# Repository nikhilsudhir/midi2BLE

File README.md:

<div align="center">

# midi2BLE

**Custom wireless MIDI adapter — ESP32-S3, LiPo powered, custom PCB**

A custom, battery-powered BLE MIDI adapter with a bespoke PCB and 3D-printed enclosure. Bridges a USB MIDI keyboard to a Mac over Bluetooth LE, eliminating the cable between instrument and computer.

[**View project page →**](https://nikhilsudhir.github.io/projects/midi2BT.html)

</div>

---

## Signal flow

<div align="center">

| **USB MIDI Keyboard** | | **ESP32-S3** | | **macOS** | | **DAW** |
|:---:|:---:|:---:|:---:|:---:|:---:|:---:|
| *(e.g. MPK Mini III)* | `── USB ──►` | *midi2BLE firmware* | `── BLE MIDI ──►` | *Audio MIDI Setup* | `──►` | *FL Studio* |

</div>

---

## Features

| | |
|---|---|
| **Wireless mode** | ESP32-S3 acts as USB host; MIDI data forwarded over BLE to macOS |
| **Passthrough mode** | Keyboard connected directly to upstream USB-C via hardware switch — ESP32 out of data path |
| **USB MIDI host** | Enumerates any class-compliant USB MIDI controller — no driver needed |
| **BLE MIDI peripheral** | Apple BLE MIDI spec, appears as a native MIDI port in Audio MIDI Setup |
| **MIDI panic** | On USB disconnect, sends Note Off + CC 123/120 for every active note on all 16 channels |
| **Auto-advertising** | Restarts BLE advertising automatically on every disconnect or reboot |
| **OLED display** | SPI-connected display shows mode, BLE status, battery %, and estimated runtime |
| **Battery management** | LiPo charge, power-path control, and ADC-based battery sense |

---

## Hardware

### Electronics

| Component | Part | Role |
|---|---|---|
| MCU / BLE | ESP32-S3-WROOM-1-N8 | Application processor, USB host, BLE MIDI |
| LiPo charger | BQ24079RGTT | 1-cell USB-C LiPo charging with power path |
| Buck regulator | TPS62162DSG | 3.3 V system rail |
| Boost converter | TLV61047DDC | 5 V VBUS supply for keyboard (wireless mode) |
| Power mux | TPS2116DRL | Battery / USB-C power-path switching |
| USB switch | TS3USB30EDGSR | Routes keyboard D+/D− to ESP32 or upstream port |
| USB ESD | PRTR5V0U2X | ESD protection on USB lines |
| Display | SPI OLED | Mode, connection status, battery info |

> Tested with an **Akai MPK Mini III**. Any USB class-compliant MIDI device should work.

### PCB

| | |
|---|---|
| Dimensions | 100 × 40 mm |
| Layers | 4 |
| Stackup | JLCPCB JLC04161H-7628 |
| Surface finish | HASL |
| Soldermask | Black |
| Mounting holes | M2.5 |

---

## Repository structure

- `main/` — Firmware (ESP-IDF / C) — see [main/README.md](main/README.md)
- `hardware/`
  - `ecad/` — KiCad schematic & PCB layout — see [hardware/ecad/README.md](hardware/ecad/README.md)
  - `mcad/` — Fusion 360 enclosure — see [hardware/mcad/README.md](hardware/mcad/README.md)
- `CMakeLists.txt`
- `sdkconfig.defaults`

---

## Build status

| Component | Status |
|---|---|
| Firmware | ✅ Complete |
| Schematic | ✅ Complete |
| PCB layout | ✅ Complete |
| Enclosure | ✅ Complete |

---

<div align="center">

[nikhilsudhir.github.io](https://nikhilsudhir.github.io/projects/midi2BLE.html)

</div>

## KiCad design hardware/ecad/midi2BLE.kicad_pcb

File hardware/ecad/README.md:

# midi2BLE

## Overview

This device is a portable USB-to-BLE MIDI bridge designed to interface with USB MIDI controllers such as the Akai MPK Mini III.

It supports two user-selectable modes:

* Wireless BLE MIDI operation
* Wired USB passthrough operation

The device is battery powered with USB-C charging and includes an onboard OLED display for status and battery information.

---

## Operating Modes

### 1. Wireless Mode

In this mode, the device acts as a BLE MIDI bridge.

#### Behavior

* ESP32-S3 operates as a USB host
* MIDI data is read from the keyboard and transmitted via BLE
* Device is powered from internal LiPo battery
* OLED displays:

  * battery percentage
  * estimated runtime
  * BLE connection status
  * keyboard connection status

#### Power

* Battery supplies system power
* Optional charging via USB-C

---

### 2. Passthrough Mode

In this mode, the device behaves as a direct USB cable between the keyboard and a computer.

#### Behavior

* Keyboard is directly connected to upstream USB-C port via hardware switching
* ESP32 is not part of the USB data path
* BLE functionality is disabled
* OLED remains active and displays:

  * "WIRED MODE"
  * charging status
  * battery percentage

#### Power

* System is powered from upstream USB-C
* Battery does NOT power the system
* Battery may still be charged

---

## Mode Selection

* A physical switch selects between:

  * WIRELESS
  * WIRED
* The switch is authoritative
* Mode switching is NOT live
* Device must be restarted after changing modes

---

## Ports

### Upstream USB-C Port

* Used for:

  * charging the device
  * connecting to a computer in passthrough mode
* Supplies system power when connected

### Keyboard USB-C Port

* Used to connect the MIDI controller
* Behavior depends on mode:

  * Wireless: connected to ESP32 USB host
  * Passthrough: connected directly to upstream USB-C

---

## Power Architecture

* 1-cell LiPo battery
* USB-C charging input
* Power-path design allows:

  * operation while charging
  * seamless transition between power sources

### Power Priorities

#### Wireless Mode

1. Battery powers system
2. USB-C supplements or charges battery

#### Passthrough Mode

1. Upstream USB-C powers system
2. Battery is isolated from load
3. Battery may still charge

---

## USB Routing

### Wireless Mode

* Keyboard D+/D- connected to ESP32 USB host

### Passthrough Mode

* Keyboard D+/D- connected directly to upstream USB-C port

This is implemented using a USB 2.0 switch/multiplexer.

---

## Keyboard Power (VBUS)

### Wireless Mode

* Supplied by internal 5V boost converter

### Passthrough Mode

* Supplied directly from upstream USB-C VBUS

---

## Display (OLED)

* SPI-connected monochrome OLED display
* Displays:

  * battery percentage
  * estimated runtime
  * current mode
  * connection status

---

## Firmware Behavior

### Wireless Mode

* USB host enabled
* BLE MIDI enabled
* MIDI data forwarded USB → BLE

### Passthrough Mode

* USB host disabled
* BLE disabled
* ESP32 used only for UI/status

---

## V1 Scope

### Included

* BLE MIDI output
* USB passthrough
* battery operation
* USB-C charging
* OLED display
* manual mode switch

### Excluded

* custom RF protocols
* MIDI remapping
* display UI complexity
* automatic mode switching
* USB hub functionality

---

## Hardware Design

The schematic and PCB layout are both complete. The design is implemented in **KiCad 10.0**.

| | |
|---|---|
| Revision | 1 |
| Schematic date | 2026-04-11 |
| PCB date | 2026-04-12 |

The schematic is split across seven sheets:

| Sheet | Description |
|---|---|
| Root | Top-level block diagram and inter-sheet connections |
| Power | LiPo charging, buck/boost regulation, and power-path control |
| ESP32_S3 | ESP32-S3-WROOM-1 module, decoupling, and GPIO assignments |
| USB Data | USB 2.0 data switching between keyboard and upstream port |
| VBUS Switching | 5V VBUS supply selection for the keyboard port |
| OLED UI | SPI OLED display and mode select switch |
| Battery Sense | Resistor divider and ADC input for battery voltage measurement |

### Key ICs

| IC | Part | Function |
|---|---|---|
| U1 | ESP32-S3-WROOM-1 | Main MCU + Wi-Fi/BLE module |
| U2 | BQ24074RGTT | 1-cell LiPo charger |
| U3 | TPS62162DSG | 3.3 V synchronous buck regulator |
| U4 | TLV61047DDC | 5 V boost converter (keyboard VBUS in wireless mode) |
| U5 | TPS2116DRL | Dual-input power mux (battery vs. USB-C power path) |
| U6 | TS3USB30EDGSR | USB 2.0 high-speed switch (keyboard data routing) |
| U7 | PRTR5V0U2X | USB ESD protection |

### PCB

The PCB is laid out in KiCad. All components are placed and fully routed.

**Board dimensions:** 75 × 40mm  
**Thickness:** 1.6mm  
**Layers:** 4  

#### Stackup

| Layer | Type | Thickness | Material |
|---|---|---|---|
| F.Cu | Signal | 35µm | Copper |
| Dielectric 1 | Prepreg | 0.1mm | FR4 |
| In1.Cu | GND plane | 35µm | Copper |
| Dielectric 2 | Core | 1.24mm | FR4 |
| In2.Cu | 3.3V power plane | 35µm | Copper |
| Dielectric 3 | Prepreg | 0.1mm | FR4 |
| B.Cu | Signal | 35µm | Copper |

Inner layers are solid copper fills: In1 = GND, In2 = SYS_3V3.

**Test points:** TP1–TP6  
**Via size:** 0.45mm diameter, 0.2mm drill

---

## Summary

This V1 design prioritizes:

* simplicity
* reliability
* clear user control

The system uses a manual mode switch and hardware-level USB routing to ensure predictable behavior and robust operation.

**Current status:** Schematic and PCB layout complete. Ready for fabrication review.

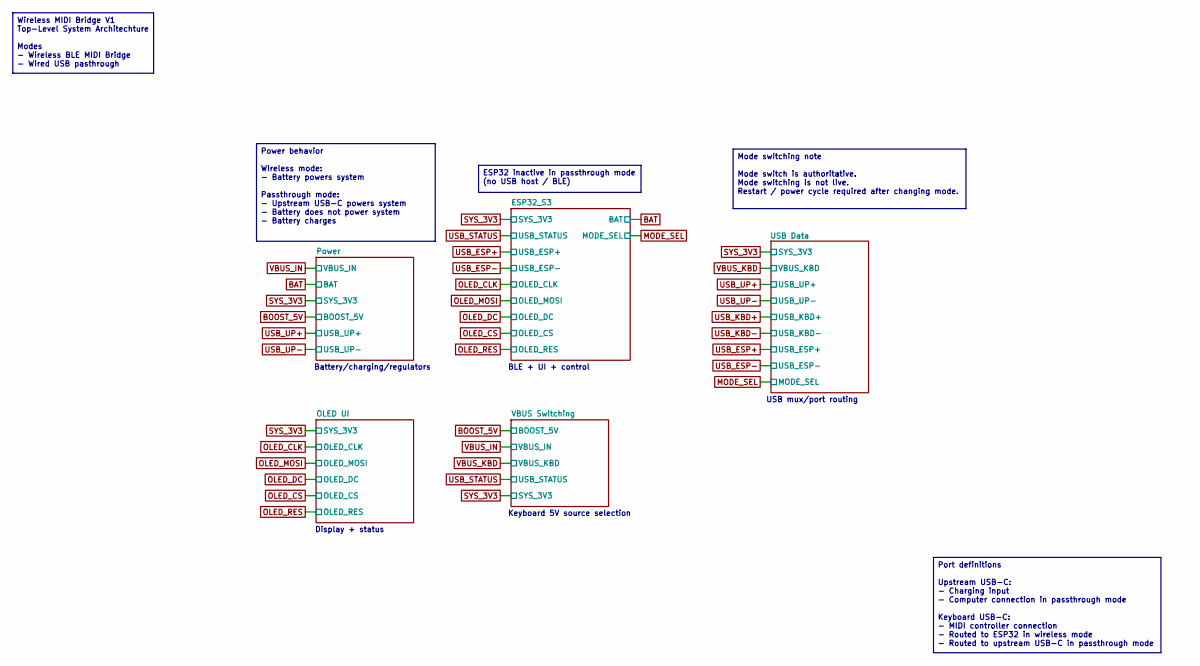
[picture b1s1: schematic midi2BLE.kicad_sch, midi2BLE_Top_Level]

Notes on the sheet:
Battery/charging/regulators
Keyboard 5V source selection
USB mux/port routing
Display + status
BLE + UI + control
Wireless MIDI Bridge V1 Top-Level System Architechture Modes - Wireless BLE MIDI Bridge - Wired USB pasthrough
Port definitions Upstream USB-C: - Charging input - Computer connection in passthrough mode Keyboard USB-C: - MIDI controller connection - Routed to ESP32 in wireless mode - Routed to upstream USB-C in passthrough mode
Mode switching note Mode switch is authoritative. Mode switching is not live. Restart / power cycle required after changing mode.
Power behavior Wireless mode: - Battery powers system Passthrough mode: - Upstream USB-C powers system - Battery does not power system - Battery charges
ESP32 inactive in passthrough mode (no USB host / BLE)

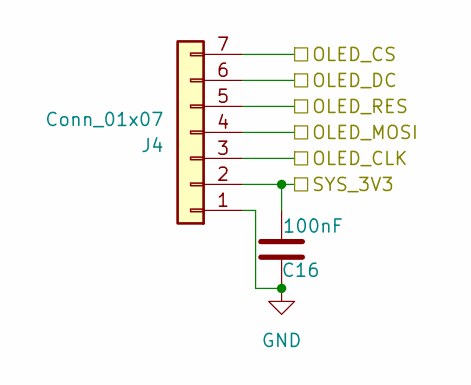
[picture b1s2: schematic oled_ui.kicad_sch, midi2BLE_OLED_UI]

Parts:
C16: 100nF; C_0603_1608Metric
J4: Conn_01x07; JST_EH_B7B-EH-A_1x07_P2.50mm_Vertical

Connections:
GND: C16.2, J4.1; also elsewhere on the board
OLED_CLK: J4.3; also elsewhere on the board
OLED_CS: J4.7; also elsewhere on the board
OLED_DC: J4.6; also elsewhere on the board
OLED_MOSI: J4.4; also elsewhere on the board
OLED_RES: J4.5; also elsewhere on the board
SYS_3V3: C16.1, J4.2; also elsewhere on the board

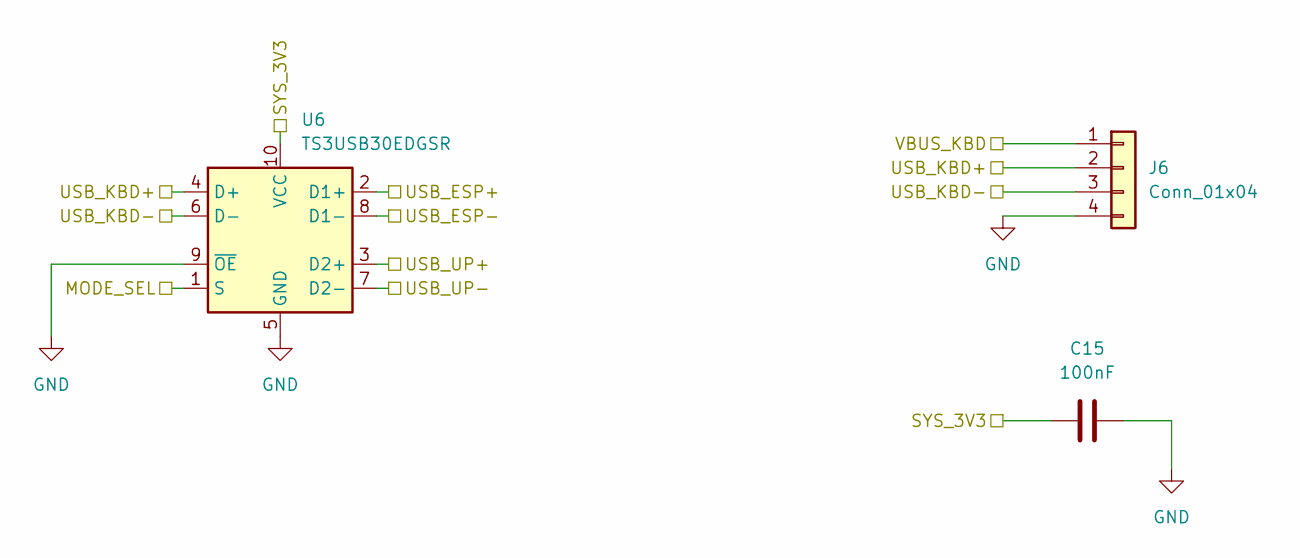
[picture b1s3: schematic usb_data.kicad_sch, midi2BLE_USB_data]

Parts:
C15: 100nF; C_0603_1608Metric
J6: Conn_01x04; JST_PH_B4B-PH-K_1x04_P2.00mm_Vertical
U6: TS3USB30EDGSR; TSSOP-10_3x3mm_P0.5mm

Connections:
GND: C15.1, J6.4, U6.5 (GND), U6.9 (~OE); also elsewhere on the board
MODE_SEL: U6.1 (S); also elsewhere on the board
SYS_3V3: C15.2, U6.10 (VCC); also elsewhere on the board
USB_ESP+: U6.2 (D1+); also elsewhere on the board
USB_ESP-: U6.8 (D1-); also elsewhere on the board
USB_KBD+: J6.2, U6.4 (D+)
USB_KBD-: J6.3, U6.6 (D-)
USB_UP+: U6.3 (D2+); also elsewhere on the board
USB_UP-: U6.7 (D2-); also elsewhere on the board
VBUS_KBD: J6.1; also elsewhere on the board

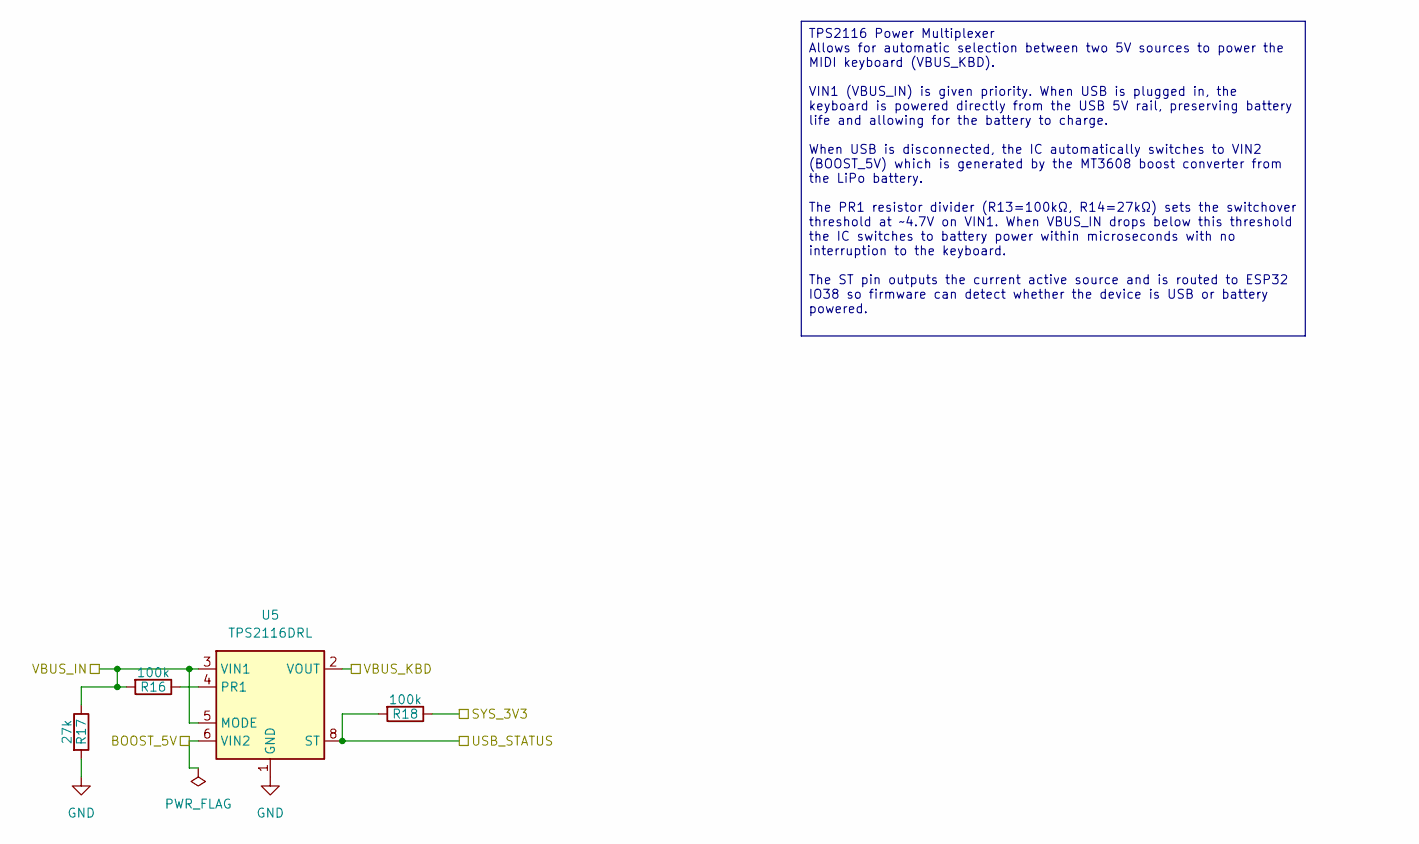
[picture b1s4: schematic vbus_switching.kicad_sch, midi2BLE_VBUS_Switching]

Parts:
R16, R18: 100k; R_0603_1608Metric
R17: 27k; R_0603_1608Metric
U5: TPS2116DRL; SOT-583-8

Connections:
BOOST_5V: U5.6 (VIN2); also elsewhere on the board
GND: R17.2, U5.1 (GND); also elsewhere on the board
unnamed: R16.1, U5.4 (PR1)
SYS_3V3: R18.1; also elsewhere on the board
USB_STATUS: R18.2, U5.8 (ST); also elsewhere on the board
VBUS_IN: R16.2, R17.1, U5.3 (VIN1), U5.5 (MODE); also elsewhere on the board
VBUS_KBD: U5.2 (VOUT), U5.7 (VOUT); also elsewhere on the board

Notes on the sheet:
TPS2116 Power Multiplexer Allows for automatic selection between two 5V sources to power the MIDI keyboard (VBUS_KBD). VIN1 (VBUS_IN) is given priority. When USB is plugged in, the keyboard is powered directly from the USB 5V rail, preserving battery life and allowing for the battery to charge. Whe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

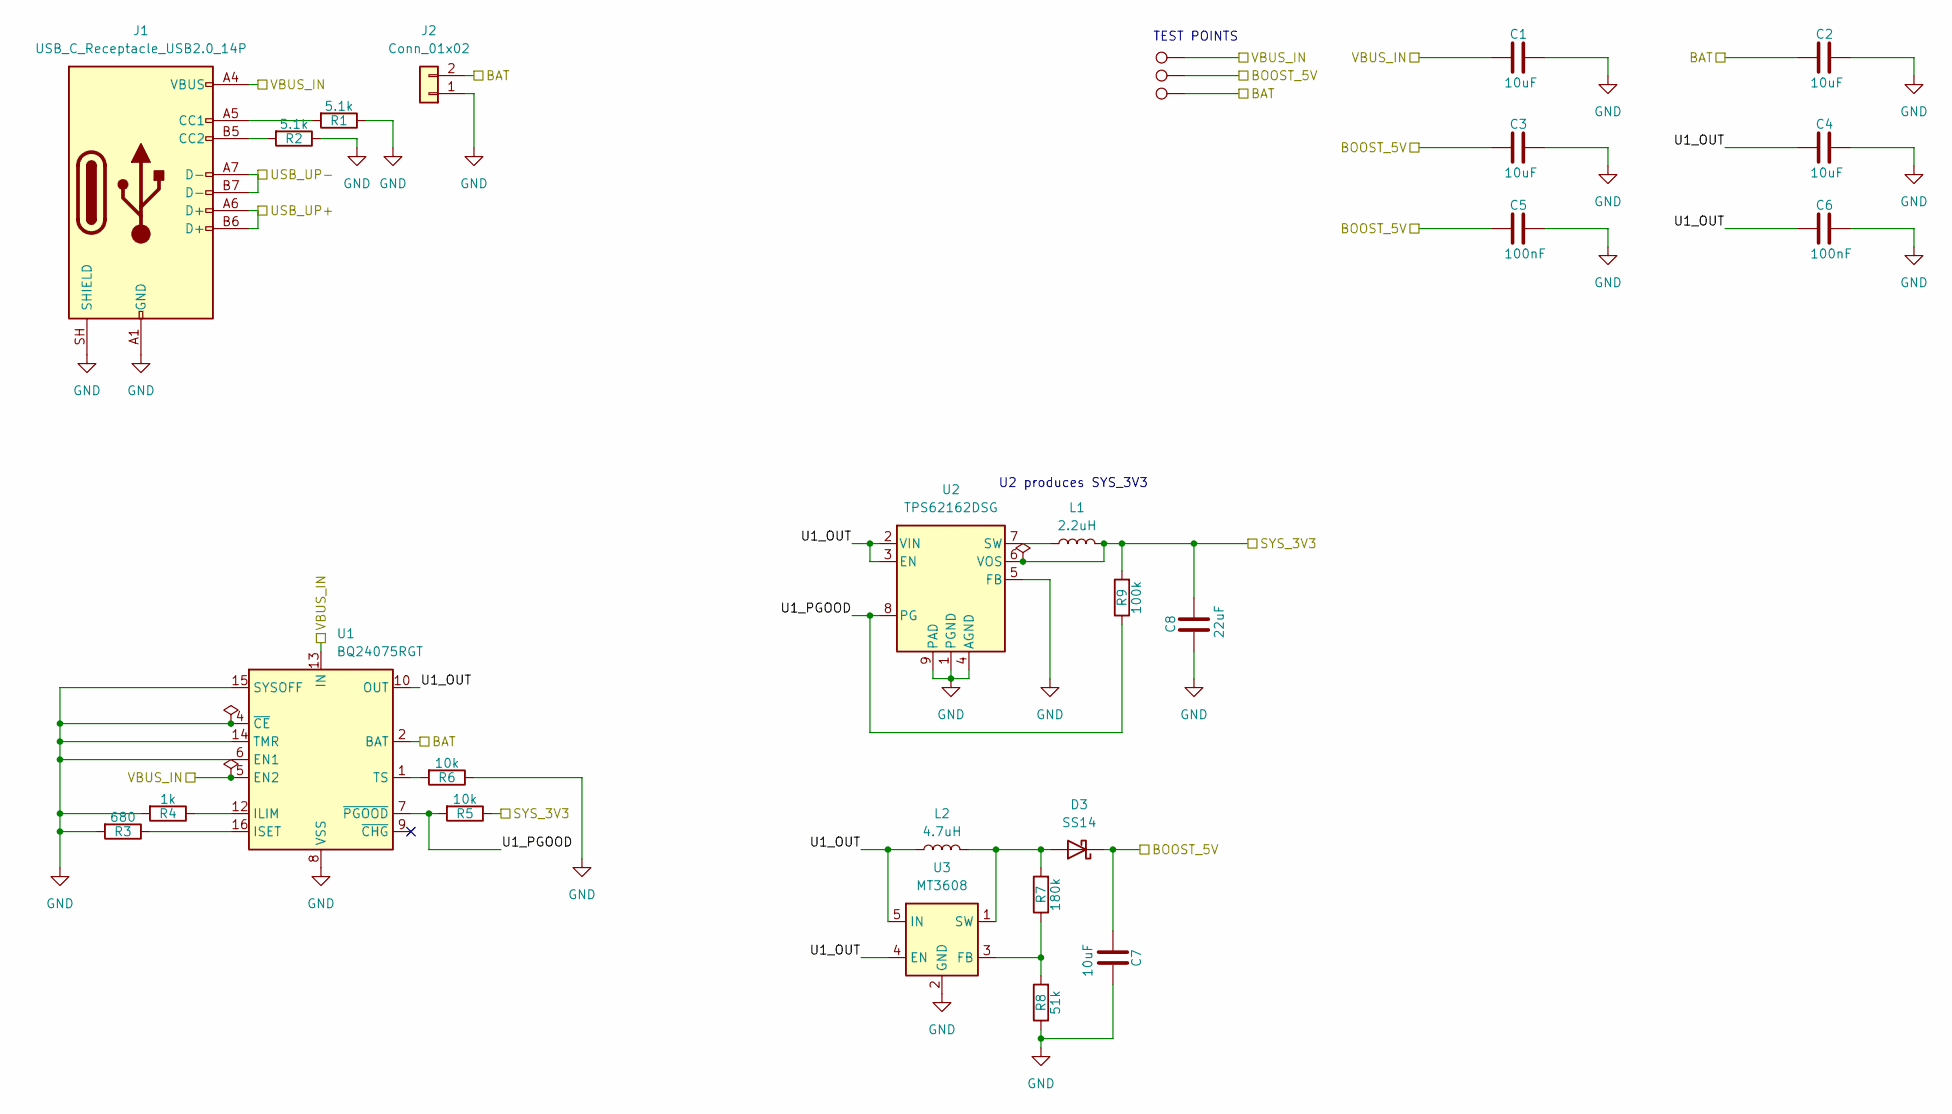
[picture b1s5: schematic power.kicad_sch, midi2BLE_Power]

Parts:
C1, C2, C3, C4, C7: 10uF; C_0603_1608Metric
C5, C6: 100nF; C_0603_1608Metric
C8: 22uF; C_0603_1608Metric
D3: SS14; D_SMA
J1: USB_C_Receptacle_USB2.0_14P; USB_C_Receptacle_G-Switch_GT-USB-7010ASV
J2: Conn_01x02; JST_PH_B2B-PH-K_1x02_P2.00mm_Vertical
L1: 2.2uH; L_1008_2520Metric
L2: 4.7uH; L_1008_2520Metric
R1, R2: 5.1k; R_0603_1608Metric
R3: 680; R_0603_1608Metric
R4: 1k; R_0603_1608Metric
R5, R6: 10k; R_0603_1608Metric
R7: 180k; R_0603_1608Metric
R8: 51k; R_0603_1608Metric
R9: 100k; R_0603_1608Metric
TP7, TP8, TP9: TestPoint; TestPoint_THTPad_D1.0mm_Drill0.5mm
U1: BQ24075RGT; VQFN-16-1EP_3x3mm_P0.5mm_EP1.6x1.6mm
U2: TPS62162DSG; WSON-8-1EP_2x2mm_P0.5mm_EP0.9x1.6mm_ThermalVias
U3: MT3608; SOT-23-6

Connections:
/Power/U1_OUT: C4.2, C6.2, L2.1, U1.10 (OUT), U1.11 (OUT), U2.2 (VIN), U2.3 (EN), U3.4 (EN), U3.5 (IN)
/Power/U1_PGOOD: R5.2, R9.1, U1.7 (~PGOOD), U2.8 (PG)
BAT: C2.2, J2.2, TP9.1 (1_1), U1.2 (BAT), U1.3 (BAT); also elsewhere on the board
BOOST_5V: C3.2, C5.2, C7.2, D3.1 (K), TP8.1 (1_1); also elsewhere on the board
GND: C1.1, C2.1, C3.1, C4.1, C5.1, C6.1, C7.1, C8.2, J1.A1 (GND), J1.A12 (GND), J1.B1 (GND), J1.B12 (GND), J1.SH (SHIELD), J2.1, R1.1, R2.1, R3.2, R4.2, R6.1, R8.1, U1.4 (~CE), U1.6 (EN1), U1.8 (VSS), U1.14 (TMR), U1.15 (SYSOFF), U1.17 (VSS), U2.1 (PGND), U2.4 (AGND), U2.5 (FB), U2.9 (PAD), U3.2 (GND); also elsewhere on the board
unnamed: D3.2 (A), L2.2, R7.2, U3.1 (SW)
unnamed: J1.A5 (CC1), R1.2
unnamed: J1.B5 (CC2), R2.2
unnamed: R4.1, U1.12 (ILIM)
unnamed: R3.1, U1.16 (ISET)
unnamed: R6.2, U1.1 (TS)
unnamed: L1.1, U2.7 (SW)
unnamed: R7.1, R8.2, U3.3 (FB)
SYS_3V3: C8.1, L1.2, R5.1, R9.2, U2.6 (VOS); also elsewhere on the board
USB_UP+: J1.A6 (D+), J1.B6 (D+); also elsewhere on the board
USB_UP-: J1.A7 (D-), J1.B7 (D-); also elsewhere on the board
VBUS_IN: C1.2, J1.A4 (VBUS), J1.A9 (VBUS), J1.B4 (VBUS), J1.B9 (VBUS), TP7.1 (1_1), U1.5 (EN2), U1.13 (IN); also elsewhere on the board

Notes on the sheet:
TEST POINTS
U2 produces SYS_3V3

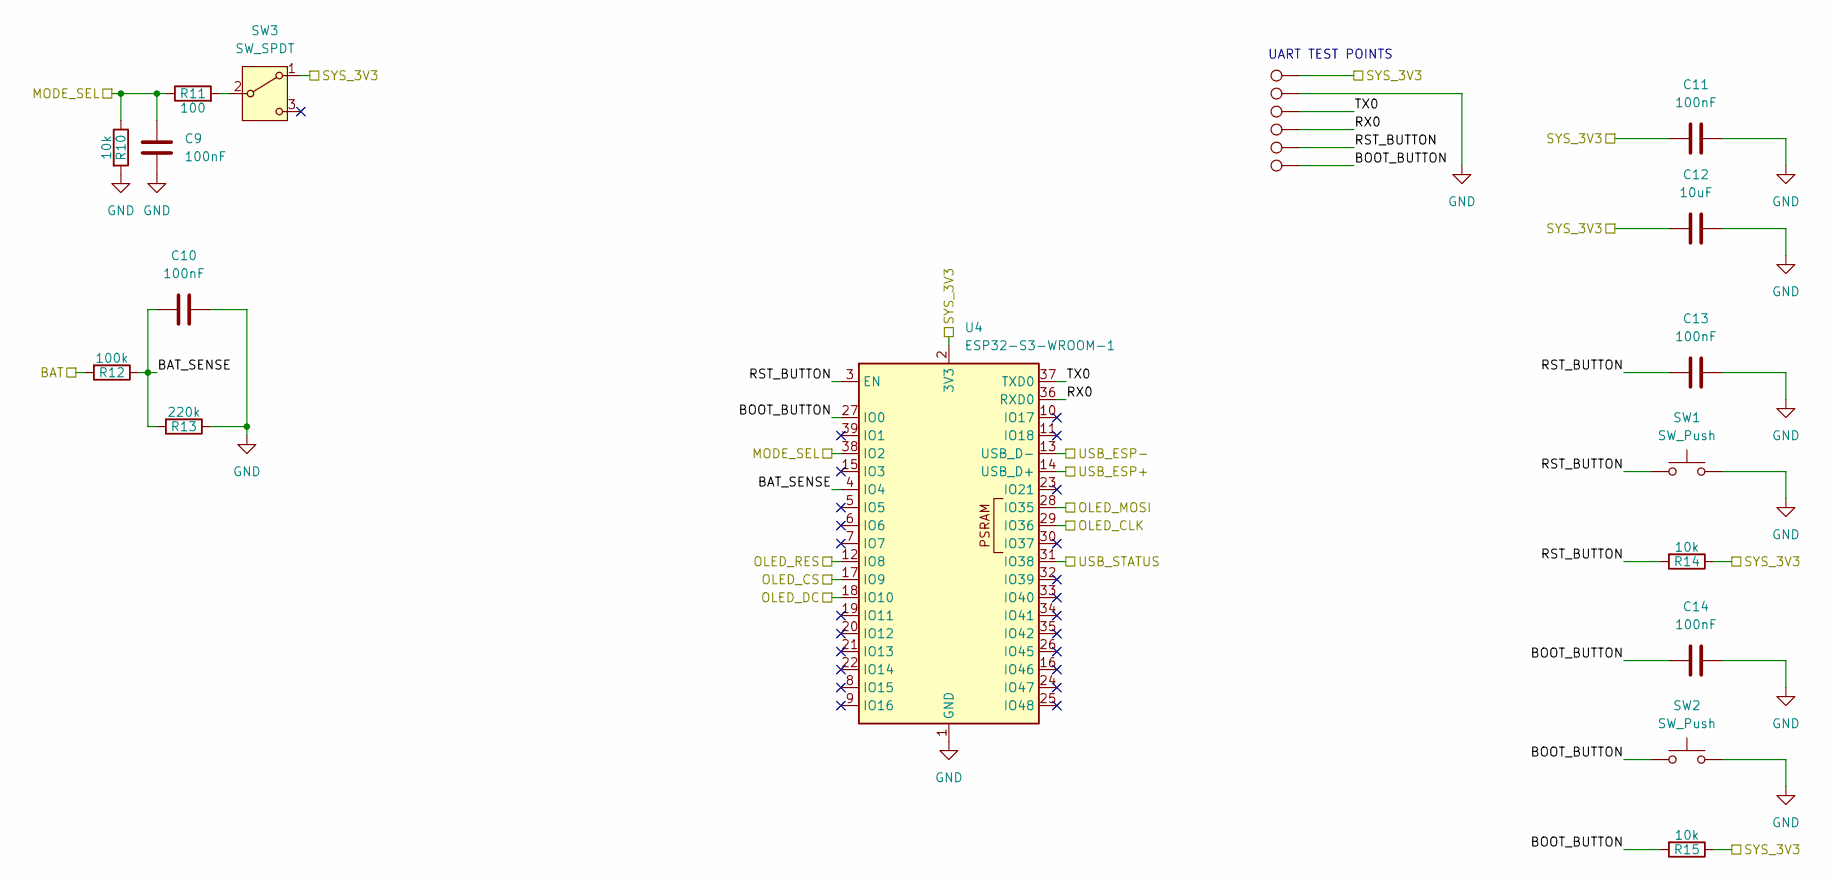
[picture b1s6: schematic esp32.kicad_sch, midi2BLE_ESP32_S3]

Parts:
C9, C10, C11, C13, C14: 100nF; C_0603_1608Metric
C12: 10uF; C_0603_1608Metric
R10, R14, R15: 10k; R_0603_1608Metric
R11: 100; R_0603_1608Metric
R12: 100k; R_0603_1608Metric
R13: 220k; R_0603_1608Metric
SW1, SW2: SW_Push; SW_SPST_B3U-1000P
SW3: SW_SPDT; SW_Slide_SPDT_Angled_CK_OS102011MA1Q
TP1, TP2, TP3, TP4, TP5, TP6: TestPoint; TestPoint_THTPad_D1.0mm_Drill0.5mm
U4: ESP32-S3-WROOM-1

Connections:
/ESP32_S3/BAT_SENSE: C10.1, R12.1, R13.2, U4.4 (IO4)
/ESP32_S3/BOOT_BUTTON: C14.1, R15.2, SW2.1, TP6.1 (1_1), U4.27 (IO0)
/ESP32_S3/RST_BUTTON: C13.1, R14.2, SW1.1, TP5.1 (1_1), U4.3 (EN)
/ESP32_S3/RX0: TP4.1 (1_1), U4.36 (RXD0)
/ESP32_S3/TX0: TP3.1 (1_1), U4.37 (TXD0)
BAT: R12.2; also elsewhere on the board
GND: C9.1, C10.2, C11.2, C12.2, C13.2, C14.2, R10.2, R13.1, SW1.2, SW2.2, TP2.1 (1_1), U4.1 (GND), U4.40 (GND), U4.41 (GND); also elsewhere on the board
MODE_SEL: C9.2, R10.1, R11.1, U4.38 (IO2); also elsewhere on the board
unnamed: R11.2, SW3.2 (B)
OLED_CLK: U4.29 (IO36); also elsewhere on the board
OLED_CS: U4.17 (IO9); also elsewhere on the board
OLED_DC: U4.18 (IO10); also elsewhere on the board
OLED_MOSI: U4.28 (IO35); also elsewhere on the board
OLED_RES: U4.12 (IO8); also elsewhere on the board
SYS_3V3: C11.1, C12.1, R14.1, R15.1, SW3.1 (A), TP1.1 (1_1), U4.2 (3V3); also elsewhere on the board
USB_ESP+: U4.14 (USB_D+); also elsewhere on the board
USB_ESP-: U4.13 (USB_D-); also elsewhere on the board
USB_STATUS: U4.31 (IO38); also elsewhere on the board

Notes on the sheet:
UART TEST POINTS

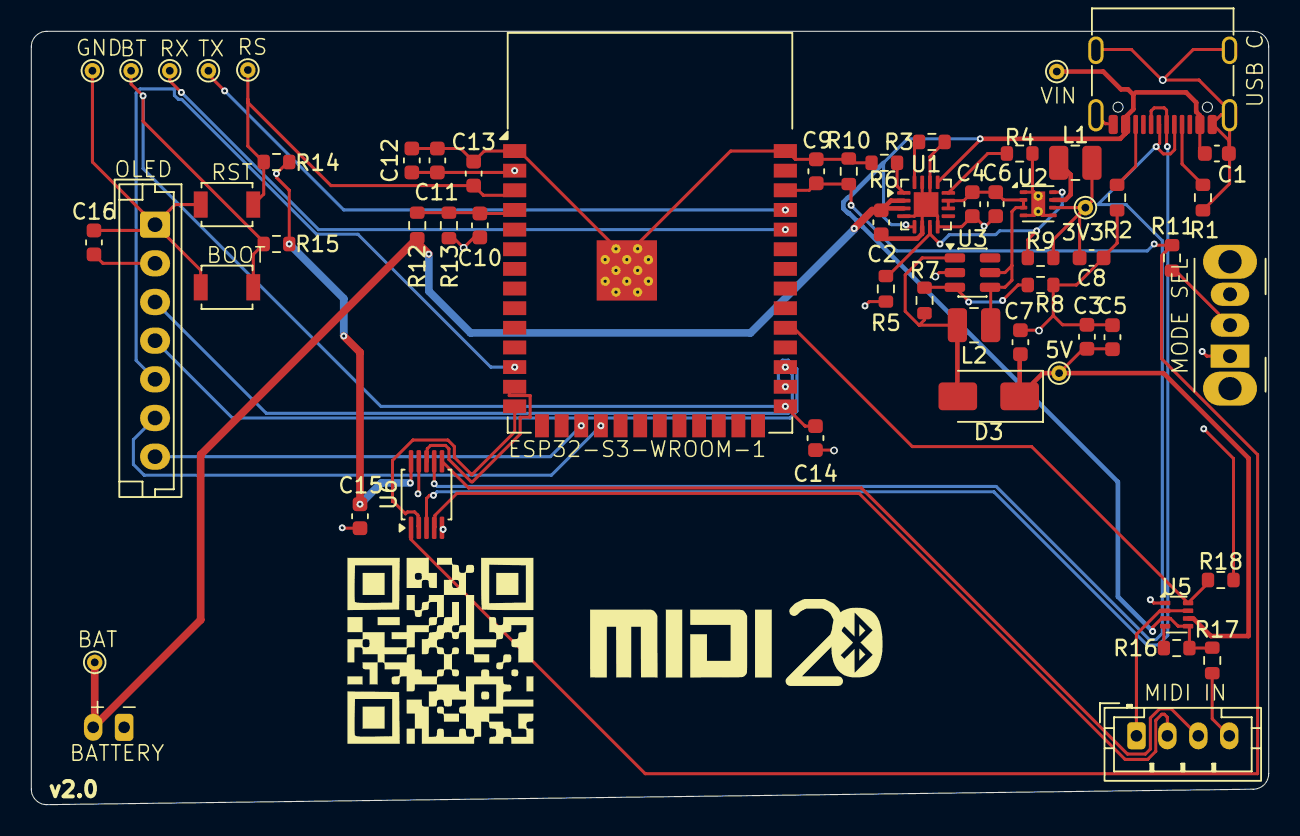
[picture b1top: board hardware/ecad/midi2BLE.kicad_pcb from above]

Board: 4 copper layers, 80.0 x 50.0 mm, 59 parts (1 on the bottom side), 36 nets.

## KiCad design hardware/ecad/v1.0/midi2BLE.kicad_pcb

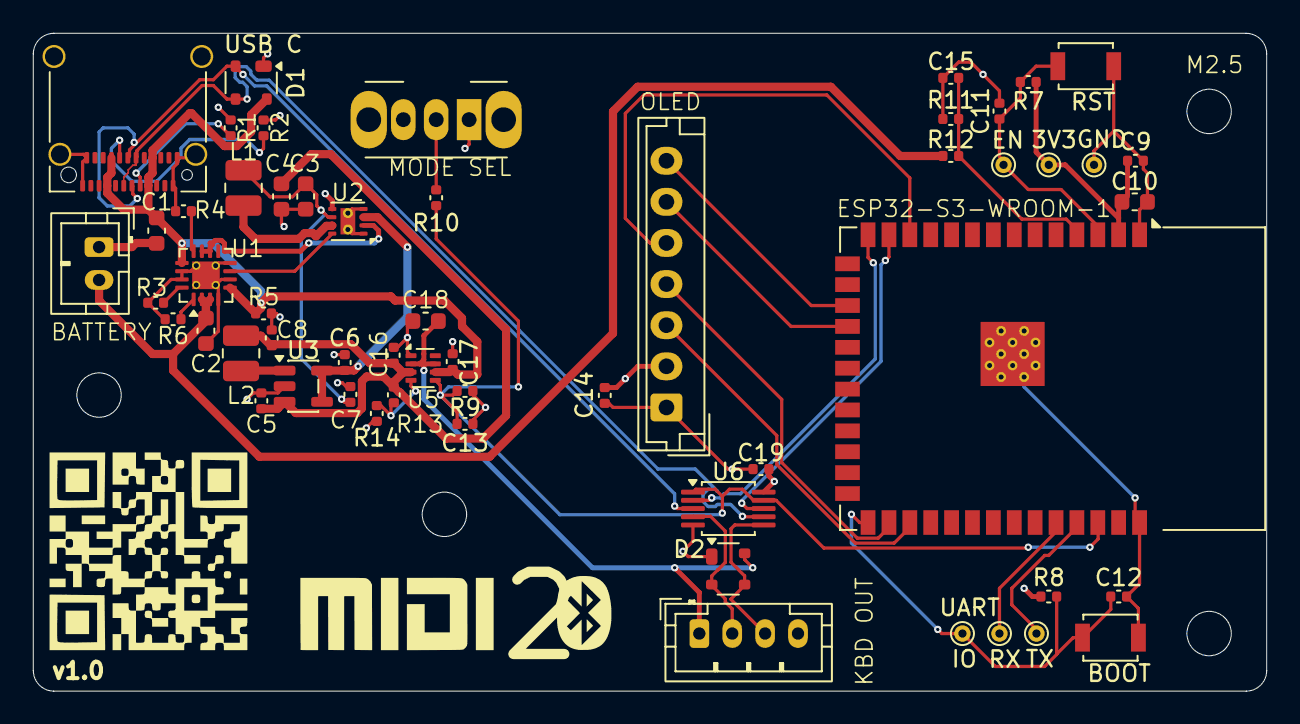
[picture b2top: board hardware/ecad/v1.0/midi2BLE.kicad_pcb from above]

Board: 4 copper layers, 75.0 x 40.0 mm, 56 parts (0 on the bottom side), 36 nets.

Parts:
C1, C2, C3, C4, C10, C18: 10uF; C_0603_1608Metric
C5, C6, C7, C8, C9, C11, C12, C13, C14, C15, C16, C17, C19: 100nF; C_0402_1005Metric
D1, D2: PRTR5V0U2X; SOT-143
J1: USB_C_Receptacle; USB_C_Receptacle_Amphenol_12401610E4-2A_CircularHoles
J2: Conn_01x02; JST_PH_B2B-PH-K_1x02_P2.00mm_Vertical
J4: Conn_01x07; JST_EH_B7B-EH-A_1x07_P2.50mm_Vertical
J6: Conn_01x04; JST_PH_B4B-PH-K_1x04_P2.00mm_Vertical
L1, L2: 2.2uH; L_1008_2520Metric
R1, R2: 5.1k; C_0402_1005Metric
R3: 590; C_0402_1005Metric
R4: 1k; C_0402_1005Metric
R5, R6, R7, R8, R9: 10k; C_0402_1005Metric
R10: 100; C_0402_1005Metric
R11: 220k; C_0402_1005Metric
R12, R13, R14: 100k; C_0402_1005Metric
SW1, SW2: SW_Push; SW_SPST_B3U-1000P
SW3: SW_SPDT; SW_Slide_SPDT_Angled_CK_OS102011MA1Q
TP1, TP2, TP3, TP4, TP5, TP6: TestPoint; TestPoint_THTPad_D1.0mm_Drill0.5mm
U1: BQ24079RGTT; VQFN-16-1EP_3x3mm_P0.5mm_EP1.68x1.68mm_ThermalVias
U2: TPS62162DSG; WSON-8-1EP_2x2mm_P0.5mm_EP0.9x1.6mm_ThermalVias
U3: TLV61047DDC; SOT-23-5
U4: ESP32-S3-WROOM-1
U5: TPS2116DRL; SOT-583-8
U6: TS3USB30EDGSR; TSSOP-10_3x3mm_P0.5mm

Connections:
/ESP32_S3/BOOT_BUTTON: C12.1, R8.2, SW2.1, TP6.1 (1_1), U4.27 (IO0)
/ESP32_S3/RST_BUTTON: C11.1, R7.2, SW1.1, TP5.1 (1_1), U4.3 (EN)
/ESP32_S3/RX0: TP4.1 (1_1), U4.36 (RXD0)
/ESP32_S3/TX0: TP3.1 (1_1), U4.37 (TXD0)
/Power/J1 CC1 - R1 P1: J1.A5 (CC1), R1.2
/Power/J1 CC2 - R2 P1: J1.B5 (CC2), R2.2
/Power/U1 ILIM - R4 P1: R4.2, U1.12 (ILIM)
/Power/U1 ISET - R3 P1: R3.2, U1.16 (ISET)
/Power/U1 OUT_2 - U2 VIN: U1.10 (OUT), U1.11 (OUT@2), U2.2 (VIN)
/Power/U1 TS - R6 P1: R6.2, U1.1 (TS)
/Power/U2 EN - U3 VIN: C6.2, U2.3 (EN), U3.4 (EN), U3.5 (VIN)
/Power/U2 FB - C3 P1: C3.2, C7.2, L1.2, U2.6 (VOS)
/Power/U2 PG - R7 P2: U1.7 (~PGOOD), U2.8 (PG)
/Power/U2 SW - L1 P1: L1.1, U2.7 (SW)
BAT: C2.2, J2.2, R12.2, U1.2 (BAT), U1.3 (BAT@2)
BAT_SENSE: C15.1, R11.2, R12.1, U4.4 (IO4)
BOOST_5V: C4.2, C5.2, C8.2, C16.1, L2.2, R13.2, U3.3 (FB), U5.3 (VIN1)
GND: C1.1, C2.1, C3.1, C4.1, C5.1, C6.1, C7.1, C8.1, C9.2, C10.2, C11.2, C12.2, C13.1, C14.2, C15.2, C16.2, C17.2, C18.2, C19.2, D1.1 (GND), D2.1 (GND), J1.A1 (GND), J1.A12 (GND), J1.B1 (GND), J1.B12 (GND), J1.SH (SHIELD), J2.1, J4.1, J6.4, R1.1, R2.1, R3.1, R4.1, R5.1, R6.1, R9.2, R11.1, R14.2, SW1.2, SW2.2, TP2.1 (1_1), U1.4 (~CE), U1.6 (EN1), U1.8 (VSS), U1.14 (TMR), U1.15 (ITERM), U1.17 (PAD), U2.1 (PGND), U2.4 (AGND), U2.9 (PAD), U3.2 (GND), U4.1 (GND), U4.40 (GND), U4.41 (GND), U5.1 (GND), U6.5 (GND)
MODE_SEL: C13.2, R9.1, R10.1, U4.38 (IO2), U5.5 (MODE), U6.1 (S), U6.9 (~OE)
unnamed: R10.2, SW3.2 (B)
unnamed: L2.1, U3.1 (SW)
unnamed: R13.1, R14.1, U5.4 (PR1)
OLED_CLK: J4.3, U4.29 (IO36)
OLED_CS: J4.7, U4.17 (IO9)
OLED_DC: J4.6, U4.18 (IO10)
OLED_MOSI: J4.4, U4.28 (IO35)
OLED_RES: J4.5, U4.12 (IO8)
SYS_3V3: C9.1, C10.1, C14.1, C19.1, J4.2, R7.1, R8.1, SW3.1 (A), TP1.1 (1_1), U2.5 (FB), U4.2 (3V3), U6.10 (VCC)
USB_ESP+: U4.14 (USB_D+), U6.2 (D1+)
USB_ESP-: U4.13 (USB_D-), U6.8 (D1-)
USB_KBD+: D2.2 (I/O1), J6.2, U6.4 (D+)
USB_KBD-: D2.3 (I/O2), J6.3, U6.6 (D-)
USB_UP+: D1.2 (I/O1), J1.A6 (D+), J1.B6 (D+), U6.3 (D2+)
USB_UP-: D1.3 (I/O2), J1.A7 (D-), J1.B7 (D-), U6.7 (D2-)
VBUS_IN: C1.2, C17.1, D1.4 (VCC), J1.A4 (VBUS), J1.A9 (VBUS), J1.B4 (VBUS), J1.B9 (VBUS), R5.2, U1.5 (EN2), U1.13 (IN), U5.6 (VIN2)
VBUS_KBD: C18.1, D2.4 (VCC), J6.1, U5.2 (VOUT), U5.7 (VOUT)

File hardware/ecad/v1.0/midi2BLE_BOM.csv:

Id,Designator,Footprint,Quantity,Designation,Supplier and ref
1,"C1, C2, C3, C4, C10, C18",C_0603_1608Metric,6,10uF,
2,"C5, C6, C7, C8, C9, C11, C12, C13, C14, C15, C16, C17, C19",C_0402_1005Metric,13,100nF,
3,"D1, D2",SOT-143,2,PRTR5V0U2X,
4,J1,USB_C_Receptacle_Amphenol_12401610E4-2A_CircularHoles,1,USB_C_Receptacle,
5,J2,JST_PH_B2B-PH-K_1x02_P2.00mm_Vertical,1,Conn_01x02,
6,J4,JST_EH_B7B-EH-A_1x07_P2.50mm_Vertical,1,Conn_01x07,
7,J6,JST_PH_B4B-PH-K_1x04_P2.00mm_Vertical,1,Conn_01x04,
8,"L1, L2",L_1008_2520Metric,2,2.2uH,
9,"R1, R2",C_0402_1005Metric,2,5.1k,
10,R3,C_0402_1005Metric,1,590,
11,R4,C_0402_1005Metric,1,1k,
12,"R5, R6, R7, R8, R9",C_0402_1005Metric,5,10k,
13,R10,C_0402_1005Metric,1,100,
14,R11,C_0402_1005Metric,1,220k,
15,"R12, R13, R14",C_0402_1005Metric,3,100k,
16,"SW1, SW2",SW_SPST_B3U-1000P,2,SW_Push,
17,SW3,SW_Slide_SPDT_Angled_CK_OS102011MA1Q,1,SW_SPDT,
19,U1,VQFN-16-1EP_3x3mm_P0.5mm_EP1.68x1.68mm_ThermalVias,1,BQ24079RGTT,
20,U2,WSON-8-1EP_2x2mm_P0.5mm_EP0.9x1.6mm_ThermalVias,1,TPS62162DSG,
21,U3,SOT-23-5,1,TLV61047DDC,
22,U4,ESP32-S3-WROOM-1,1,ESP32-S3-WROOM-1,
23,U5,SOT-583-8,1,TPS2116DRL,
24,U6,TSSOP-10_3x3mm_P0.5mm,1,TS3USB30EDGSR,

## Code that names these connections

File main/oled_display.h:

#pragma once

#include <stdint.h>
#include <stdbool.h>
#include "mode_manager.h"
#include "driver/gpio.h"

// SPI pins — adjust to match PCB once schematic is finalised
#define OLED_CLK   GPIO_NUM_36
#define OLED_MOSI  GPIO_NUM_35
#define OLED_DC    GPIO_NUM_10   // Data/Command select
#define OLED_CS    GPIO_NUM_9    // Chip select
#define OLED_RES   GPIO_NUM_8    // Hardware reset

/**
 * Initialise the SSD1306 over I2C and clear the display.
 * Safe to call even if no display is physically connected — subsequent calls
 * will silently no-op if initialisation fails.
 */
void oled_init(void);

// ---- State setters (callable from any task) ---------------------------------

void oled_set_mode(device_mode_t mode);
void oled_set_ble_connected(bool connected);

/**
 * @param connected   true when a USB MIDI device is enumerated
 * @param device_name Product string from the USB descriptor, or "" if unavailable.
 *                    Truncated to 21 characters on screen.
 */
void oled_set_usb_connected(bool connected, const char *device_name);

/** Call each time a MIDI packet is received — clears automatically after redraw. */
void oled_set_midi_active(bool active);

void oled_set_battery(uint8_t percent);

// ---- Display actions --------------------------------------------------------

/**
 * Show "MODE CHANGED / RESTARTING..." for ~2 s.
 * Intended to be called just before esp_restart().
 */
void oled_show_mode_change(void);

/**
 * Redraw the full screen from current state and push to hardware.
 * Call at ~1 Hz from the OLED update task.
 */
void oled_update(void);

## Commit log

2026-04-10 ESP32 works as a UBS pass thorugh to the serial monitor now!
2026-04-10 Moved into the main repo
2026-04-10 AKAI MPK MKIII fully working BLE connection
2026-04-10 Cleaning up the repository by removing the .devcontainer directory and related files, and adding BLE MIDI functionality to the main application. Updated CMakeLists.txt and .gitignore accordingly.
2026-04-10 Updated firmware to include builtin panic button in case keyboard dies
2026-04-10 Added license., changelog and updated the readme
2026-04-10 Updated Readme, created ecad and mcad folders
2026-04-10 Split off Readme into each section of the project
2026-04-10 Added License
2026-04-11 Add OLED display, mode switch, and battery monitor
    - New modules: mode_manager, oled_display, battery
    - Mode switch on GPIO2 reads at boot; NVS detects changes and restarts cleanly
    - SH1106 SPI OLED driver with 5x7 font, page-by-page writes, 180° rotation
    - Status screens for WIRELESS and PASSTHROUGH modes
    - USB device name built from manufacturer + product descriptor strings
    - Battery ADC on GPIO4 with voltage divider; bar and percentage on display
2026-04-11 Add MCAD enclosure v1 and update docs
    - Enclosure body v1 in Fusion 360 — USB-B cutout, fitment verified against keyboard
    - Updated MCAD README and changelog
2026-04-11 Initial KiCad project import
2026-04-11 Finsihed power schematic, but needs work... pcb has lots of errors still
2026-04-12 Updated code for battery readout
2026-04-12 Reassigned OLED SPI pins away from Octal flash GPIOs (GPIO11/12) and move BAT_SENSE to ADC1 to avoid BLE/ADC2 conflict
2026-04-12 Power schematic finished, top level schematic editied to swap from I2c to SPI instead
2026-04-13 finsihed 6/7 sheets, usb_data needs work. Some warnings to be dealt with aswell but no hard errors.
2026-04-14 Updated schematics to get rid of errors and warnings
2026-04-14 feat: complete schematic design for midi2BLE v1
    - Add 7-sheet hierarchical schematic covering full system architecture
    - Power sheet: BQ24079RGTT charger, TPS62162DSG 3.3V buck, TLV61047DDC
    5V boost, PRTR5V0U2X ESD protection, USB-C receptacle with CC resistors
    - ESP32-S3 sheet: WROOM-1-N8R2 module, UART header, boot/reset buttons,
    MODE_SEL debounce circuit, BAT_SENSE ADC input
    - OLED UI sheet: SPI SSD1306 connector (GPIO35/36/10/9/8)
2026-04-14 update READMEs
2026-04-14 Updated schematics and added printed pdf
2026-04-14 docs(hardware): update ecad README to reflect completed schematic and PCB — PCB IS DONE!!!
2026-04-15 Updated KiCad projectm and pcb, added in BOM
2026-04-20 readmes and changelog update
2026-05-01 Fix link case in README.md
2026-05-15 fix: resolve fatal power and USB switching errors
    Replace TLV61047 boost converter with MT3608; add SS14 catch diode, 4.7µH inductor, and correct FB divider (180kΩ/51kΩ) for 5V output
    Fix TPS62162DSG EN circular dependency; connect directly to U1_OUT
    Fix TPS62162DSG FB pin; disconnect from SYS_3V3 and tie to GND
    Fix TPS2116 power mux; remove series resistor on VIN1, add correct PR1 divider (100kΩ/27kΩ), tie MODE to VIN1 for priority mode
    Fix TS3USB30E OE pin; tie directly to GND to keep switch always enabled
    Add PGOOD pull-up resistor (10kΩ) to SYS_3V3 on BQ24079
2026-05-16 Fixed minor errors and smaller issues withing schematics, moved v1 pcb and specific projet artifacts to archive. Produced PDF of full schematic
2026-05-26 Fixed minor errors and smaller issues withing schematics, moved v1 pcb and specific projet artifacts to archive. Updated changelog and finsihed pcb fopr version 2

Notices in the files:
README.md:
License: MIT
